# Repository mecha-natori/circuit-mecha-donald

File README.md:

# メカドナルド

メカドナルドはSTM32F303ZDT6を使用したPWM MD駆動基板です。

エンコーダーを接続

## 仕様

|        機能         | 個数 | 備考                                            |
| :-----------------: | ---: | :---------------------------------------------- |
|         MCU         |    1 | STM32F303ZDT6                                   |
|       ST-LINK       |    1 | ピンアサインはSWD                               |
|         CAN         |    2 | 電源ピンは5V、Classic CANのみ対応、1系統から2個 |
|        UART         |    1 | 電源ピンは5V、USART1つ                          |
|       PWM MD        |    6 | 対応するエンコーダの端子と横並び                |
|     エンコーダ      |    6 | 電源ピンは5V、対応するPWM MDの端子と横並び      |
|  リセットスイッチ   |    1 |                                                 |
| 5V-3.3Vレギュレータ |    1 | 外部電源からの供給用                            |
|     寸法(外形)      |      | 111mm x 86mm                                    |
|   寸法(ネジ穴間)    |      | 100mm x 75mm                                    |

## 名前の由来

メカ+ドナルドです。他意はありません。 I'm burnin' it! (迫真)

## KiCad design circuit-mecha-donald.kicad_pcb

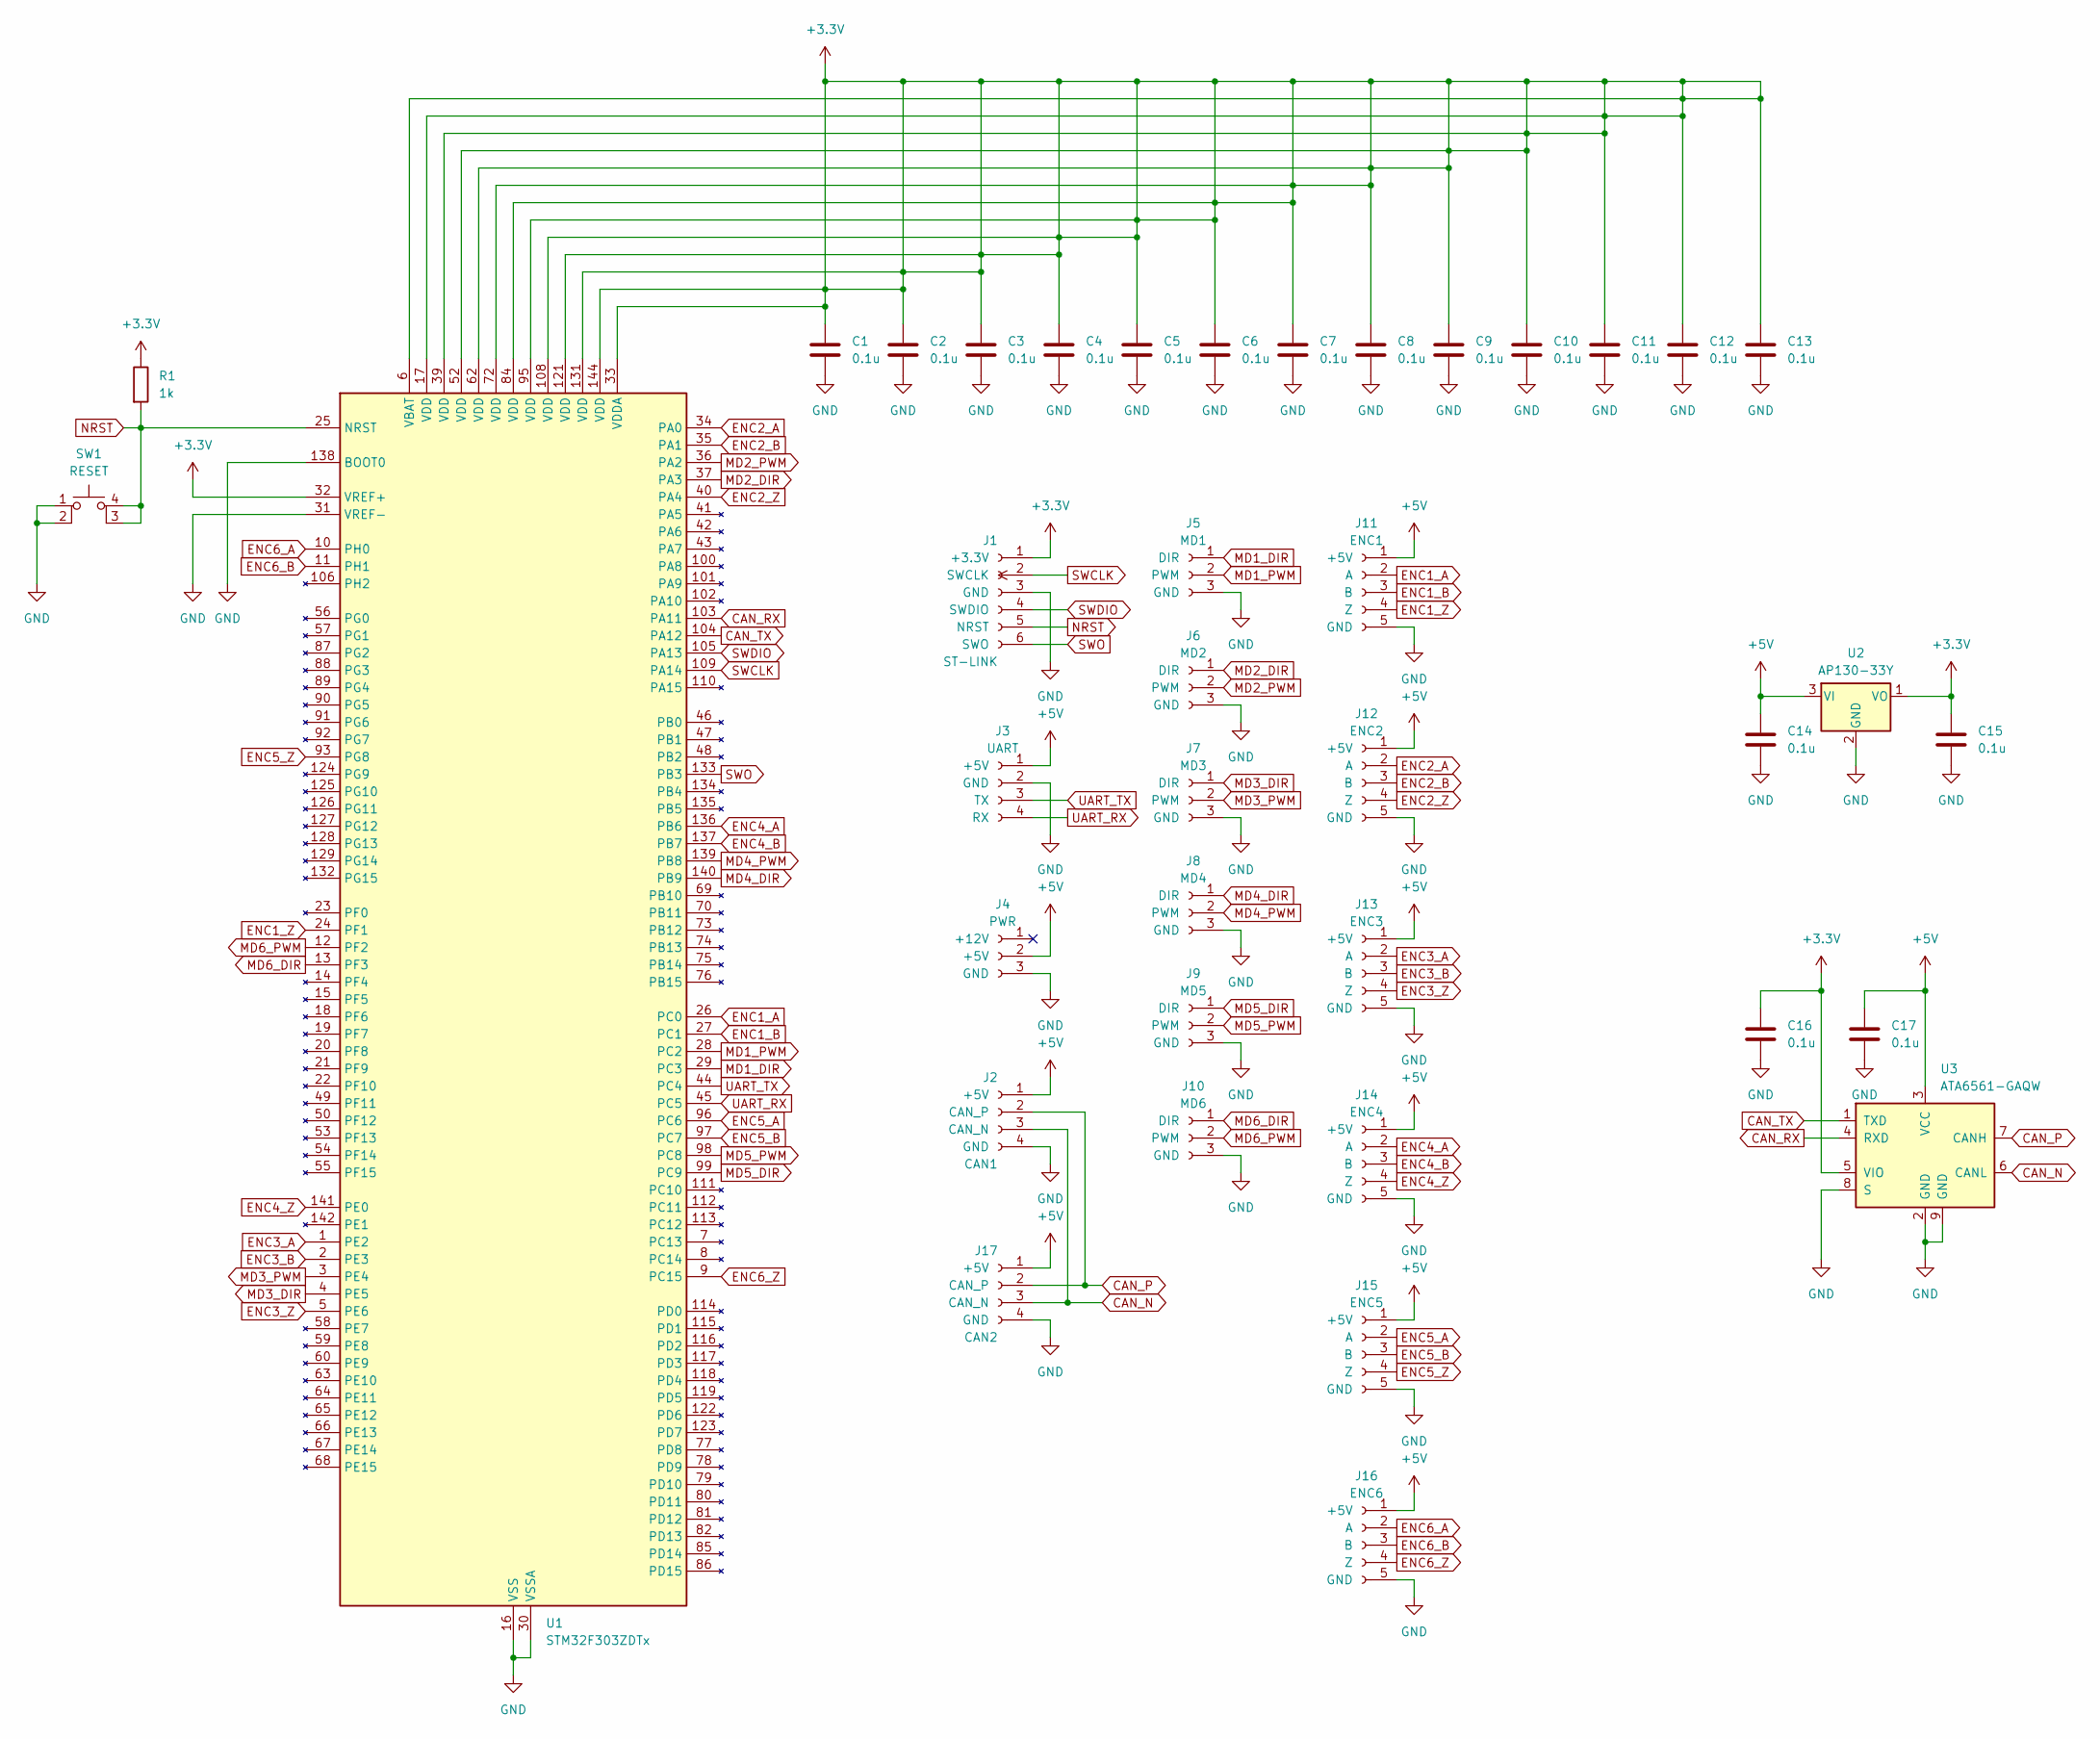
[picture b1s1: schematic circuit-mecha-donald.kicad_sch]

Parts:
C1, C2, C3, C4, C5, C6, C7, C8, C9, C10, C11, C12, C13, C14, C15, C16, C17: 0.1u; C_0603_1608Metric_Pad1.08x0.95mm_HandSolder
J1: ST-LINK; JST_ZH_B6B-ZR_1x06_P1.50mm_Vertical
J2: CAN1; JST_XA_B04B-XASK-1_1x04_P2.50mm_Vertical
J3: UART; DF1B-4P-2.5DSA
J4: PWR; JST_XH_B3B-XH-A_1x03_P2.50mm_Vertical
J5: MD1; JST_XA_B03B-XASK-1_1x03_P2.50mm_Vertical
J6: MD2; JST_XA_B03B-XASK-1_1x03_P2.50mm_Vertical
J7: MD3; JST_XA_B03B-XASK-1_1x03_P2.50mm_Vertical
J8: MD4; JST_XA_B03B-XASK-1_1x03_P2.50mm_Vertical
J9: MD5; JST_XA_B03B-XASK-1_1x03_P2.50mm_Vertical
J10: MD6; JST_XA_B03B-XASK-1_1x03_P2.50mm_Vertical
J11: ENC1; JST_PA_B05B-PASK-1_1x05_P2.00mm_Vertical
J12: ENC2; JST_PA_B05B-PASK-1_1x05_P2.00mm_Vertical
J13: ENC3; JST_PA_B05B-PASK-1_1x05_P2.00mm_Vertical
J14: ENC4; JST_PA_B05B-PASK-1_1x05_P2.00mm_Vertical
J15: ENC5; JST_PA_B05B-PASK-1_1x05_P2.00mm_Vertical
J16: ENC6; JST_PA_B05B-PASK-1_1x05_P2.00mm_Vertical
J17: CAN2; JST_XA_B04B-XASK-1_1x04_P2.50mm_Vertical
R1: 1k; R_0603_1608Metric_Pad0.98x0.95mm_HandSolder
SW1: RESET; tact
U1: STM32F303ZDTx; LQFP-144_20x20mm_P0.5mm
U2: AP130-33Y; SOT-89-3
U3: ATA6561-GAQW; SOIC-8-1EP_3.9x4.9mm_P1.27mm_EP2.95x4.9mm_Mask2.71x3.4mm

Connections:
+3.3V: C1.1, C2.1, C3.1, C4.1, C5.1, C6.1, C7.1, C8.1, C9.1, C10.1, C11.1, C12.1, C13.1, C15.1, C16.1, J1.1 (+3.3V), R1.1, U1.6 (VBAT), U1.17 (VDD), U1.32 (VREF+), U1.33 (VDDA), U1.39 (VDD), U1.52 (VDD), U1.62 (VDD), U1.72 (VDD), U1.84 (VDD), U1.95 (VDD), U1.108 (VDD), U1.121 (VDD), U1.131 (VDD), U1.144 (VDD), U2.1 (VO), U3.5 (VIO)
+5V: C14.1, C17.1, J2.1 (+5V), J3.1 (+5V), J4.2 (+5V), J11.1 (+5V), J12.1 (+5V), J13.1 (+5V), J14.1 (+5V), J15.1 (+5V), J16.1 (+5V), J17.1 (+5V), U2.3 (VI), U3.3 (VCC)
CAN_N: J2.3 (CAN_N), J17.3 (CAN_N), U3.6 (CANL)
CAN_P: J2.2 (CAN_P), J17.2 (CAN_P), U3.7 (CANH)
CAN_RX: U1.103 (PA11), U3.4 (RXD)
CAN_TX: U1.104 (PA12), U3.1 (TXD)
ENC1_A: J11.2 (A), U1.26 (PC0)
ENC1_B: J11.3 (B), U1.27 (PC1)
ENC1_Z: J11.4 (Z), U1.24 (PF1)
ENC2_A: J12.2 (A), U1.34 (PA0)
ENC2_B: J12.3 (B), U1.35 (PA1)
ENC2_Z: J12.4 (Z), U1.40 (PA4)
ENC3_A: J13.2 (A), U1.1 (PE2)
ENC3_B: J13.3 (B), U1.2 (PE3)
ENC3_Z: J13.4 (Z), U1.5 (PE6)
ENC4_A: J14.2 (A), U1.136 (PB6)
ENC4_B: J14.3 (B), U1.137 (PB7)
ENC4_Z: J14.4 (Z), U1.141 (PE0)
ENC5_A: J15.2 (A), U1.96 (PC6)
ENC5_B: J15.3 (B), U1.97 (PC7)
ENC5_Z: J15.4 (Z), U1.93 (PG8)
ENC6_A: J16.2 (A), U1.10 (PH0)
ENC6_B: J16.3 (B), U1.11 (PH1)
ENC6_Z: J16.4 (Z), U1.9 (PC15)
GND: C1.2, C2.2, C3.2, C4.2, C5.2, C6.2, C7.2, C8.2, C9.2, C10.2, C11.2, C12.2, C13.2, C14.2, C15.2, C16.2, C17.2, J1.3 (GND), J2.4 (GND), J3.2 (GND), J4.3 (GND), J5.3 (GND), J6.3 (GND), J7.3 (GND), J8.3 (GND), J9.3 (GND), J10.3 (GND), J11.5 (GND), J12.5 (GND), J13.5 (GND), J14.5 (GND), J15.5 (GND), J16.5 (GND), J17.4 (GND), SW1.1, SW1.2, U1.16 (VSS), U1.30 (VSSA), U1.31 (VREF-), U1.38 (VSS), U1.51 (VSS), U1.61 (VSS), U1.71 (VSS), U1.83 (VSS), U1.94 (VSS), U1.107 (VSS), U1.120 (VSS), U1.130 (VSS), U1.138 (BOOT0), U1.143 (VSS), U2.2 (GND), U3.2 (GND), U3.8 (S), U3.9 (GND)
MD1_DIR: J5.1 (DIR), U1.29 (PC3)
MD1_PWM: J5.2 (PWM), U1.28 (PC2)
MD2_DIR: J6.1 (DIR), U1.37 (PA3)
MD2_PWM: J6.2 (PWM), U1.36 (PA2)
MD3_DIR: J7.1 (DIR), U1.4 (PE5)
MD3_PWM: J7.2 (PWM), U1.3 (PE4)
MD4_DIR: J8.1 (DIR), U1.140 (PB9)
MD4_PWM: J8.2 (PWM), U1.139 (PB8)
MD5_DIR: J9.1 (DIR), U1.99 (PC9)
MD5_PWM: J9.2 (PWM), U1.98 (PC8)
MD6_DIR: J10.1 (DIR), U1.13 (PF3)
MD6_PWM: J10.2 (PWM), U1.12 (PF2)
NRST: J1.5 (NRST), R1.2, SW1.3 (K), SW1.4 (A), U1.25 (NRST)
SWCLK: J1.2 (SWCLK), U1.109 (PA14)
SWDIO: J1.4 (SWDIO), U1.105 (PA13)
SWO: J1.6 (SWO), U1.133 (PB3)
UART_RX: J3.4 (RX), U1.45 (PC5)
UART_TX: J3.3 (TX), U1.44 (PC4)

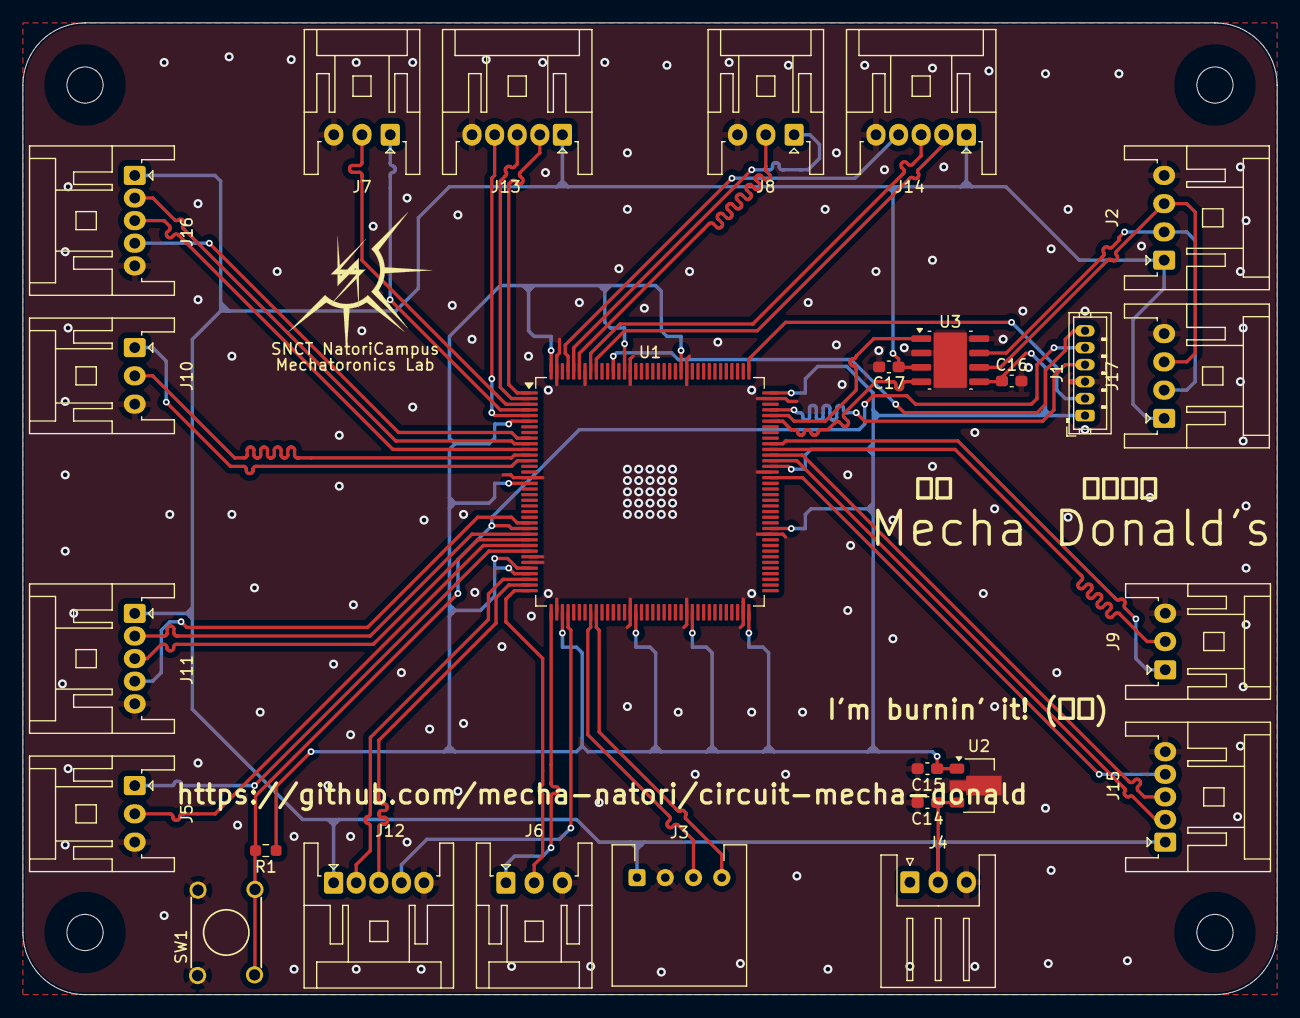
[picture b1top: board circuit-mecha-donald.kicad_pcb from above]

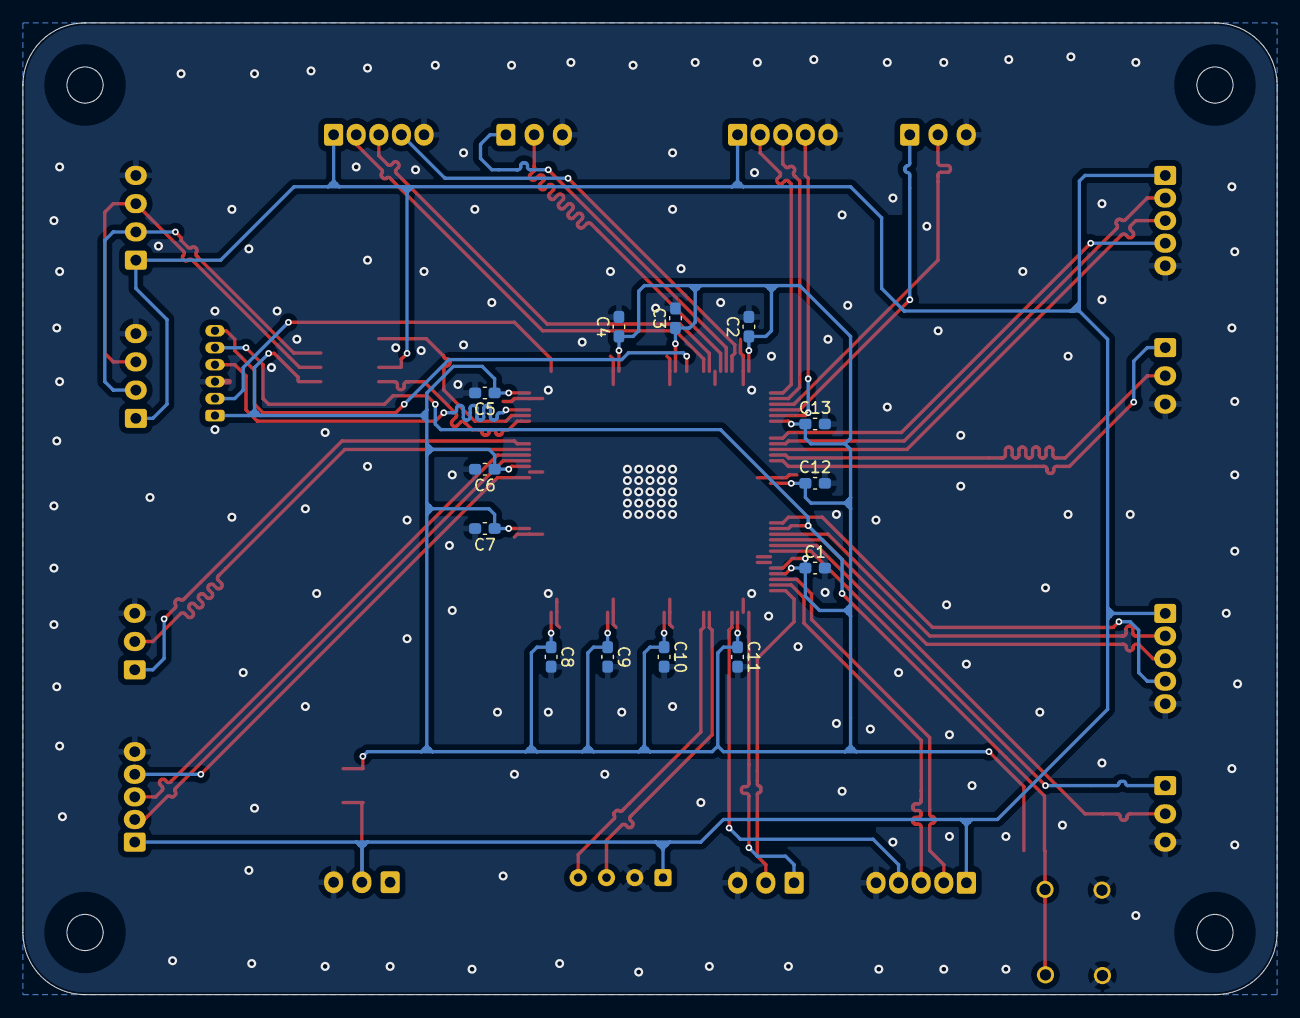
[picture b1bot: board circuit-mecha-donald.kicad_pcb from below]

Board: 2 copper layers, 111.0 x 86.0 mm, 43 parts (13 on the bottom side), 43 nets.

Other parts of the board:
 : holeφ3.2
 #2,  #3,  #4: holeφ3.2

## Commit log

2025-07-15 feature: CANコネクタを追加。
